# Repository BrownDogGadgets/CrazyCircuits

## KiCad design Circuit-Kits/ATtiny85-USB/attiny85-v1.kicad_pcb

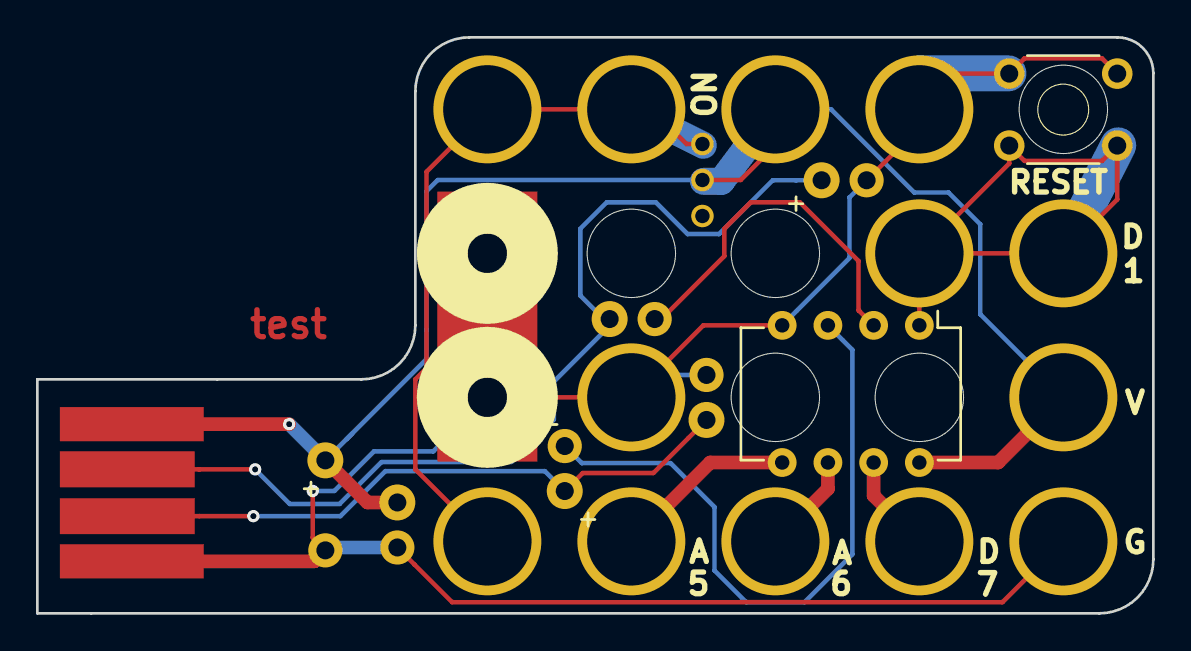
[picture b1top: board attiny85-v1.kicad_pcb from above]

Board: 2 copper layers, 62.0 x 32.0 mm, 18 parts (0 on the bottom side), 11 nets.

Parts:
BT1: Battery; CR2032-1x4
C1: 100nF; STANDALONE-2.54MM-TH
C2: 10uF; STANDALONE-5MM-TH
D1, D2: Z3v6; STANDALONE-2.54MM-TH
IC1: ATTINY85-P; DIP8-PLATFORM-TEST-NARROW
P1, P5, P6, P7: TEST_1P; STANDALONE-LEGO-HOLE-PLATED
P2: USB_PCB; USB-A-PCB-TRACES
PAD: HOLE; STANDALONE-LEGO-HOLE-PLATED
PAD#2, PAD#3: HOLE; STANDALONE-LEGO-HOLE-PLATED
R1, R2: 220; STANDALONE-2.54MM-TH
SW1: SW_PUSH; BUTTON-1x3-90DEGREE-TH-OMRON-B3F-1XXX
SW2: SLIDE; SWITCH-SPDT-3PIN-2.5mmPITCH-TH-2x2-A

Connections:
GND: BT1.GND, C1.2, C2.2, D1.2, D2.2, IC1.4, P2.4, PAD#2.1, PAD#3.1, SW1.1
unnamed: BT1.1, SW2.3
unnamed: D1.1, P2.3, R2.1
unnamed: D2.1, P2.2, R1.1
unnamed: IC1.1, P1.1, SW1.2
unnamed: IC1.2, R1.2
unnamed: IC1.3, R2.2
unnamed: IC1.5, P5.1
unnamed: IC1.6, P6.1
unnamed: IC1.7, P7.1
VCC: C1.1, C2.1, IC1.8, P2.1, PAD.1, SW2.2

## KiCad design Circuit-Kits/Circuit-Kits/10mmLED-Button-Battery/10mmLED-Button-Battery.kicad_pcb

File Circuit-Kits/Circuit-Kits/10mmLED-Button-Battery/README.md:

<!--- start title --->
# 10mmLED-Button-Battery Circuit Kit v1.3

- Updated: 7 Oct 2017

- Website: http://browndoggadgets.com/
- Company: Brown Dog Gadgets
- License: All rights reserved.

<!--- end title --->

Circuit kit that can be snapped apart into three Lego-compatible modules. Just add a coin cell battery and light the LED by pressing the pushbutton.

<!--- start bom --->

|Ref|Qty|Description|Digikey PN|
|---|---|-----------|------|
|BT1|1|HOLDER BATT COIN CR2032/20MM|952-1735-1-ND|
|LED1|1|LED GREEN 10MM DIA 2.54MM PITCH TH|754-1898-ND|
|SW1|1|SWITCH TACTILE SPST-NO 0.05A 24V|SW400-ND|

<!--- end bom --->

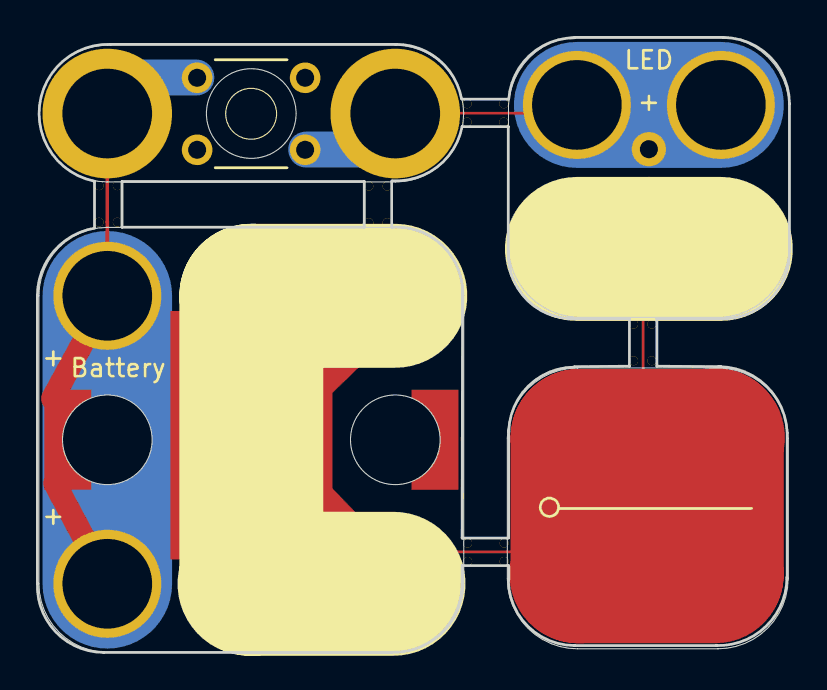
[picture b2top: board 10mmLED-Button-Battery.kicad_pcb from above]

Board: 2 copper layers, 41.8 x 34.2 mm, 4 parts (0 on the bottom side), 3 nets.

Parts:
BT1: Battery; CR2032-3x3
LED1: LED; LED-2.54MM-TH-2x2
LOGO: Val**; LOGO-CRAZY-2x2
SW1: Pushbutton; BUTTON-1x3-TH-OMRON-B3F-1XXX

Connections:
+3V: BT1.+, SW1.1
GND: BT1.GND, LED1.-
unnamed: LED1.+, SW1.2

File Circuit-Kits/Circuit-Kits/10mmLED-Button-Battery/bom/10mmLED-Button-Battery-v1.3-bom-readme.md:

|Ref|Qty|Description|Digikey PN|
|---|---|-----------|------|
|BT1|1|HOLDER BATT COIN CR2032/20MM|952-1735-1-ND|
|LED1|1|LED GREEN 10MM DIA 2.54MM PITCH TH|754-1898-ND|
|SW1|1|SWITCH TACTILE SPST-NO 0.05A 24V|SW400-ND|

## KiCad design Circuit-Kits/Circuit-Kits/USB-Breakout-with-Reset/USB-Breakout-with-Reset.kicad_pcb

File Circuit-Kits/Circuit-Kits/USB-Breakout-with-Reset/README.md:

<!--- start title --->
# USB-Breakout-with-Reset v1.0

- Updated: 14 Feb 2017
- Website: http://browndoggadgets.com/
- Company: Brown Dog Gadgets
- License: All rights reserved.

<!--- end title --->

Circuit kit module to break out USB + and - signals, along with a RESET pushbutton, to program Rewire Circuit microcontrollers in place. 

<!--- start bom --->

|Refdes|Qty|Description|Digikey Number|
|------|---|-----------|--------------|
|C1|1|CAP CER 1UF 16V X7R RADIAL|445-8614-ND|
|D1,D2|2|DIODE ZENER 3.6V 1W DO41|BZX85C3V6-ND|
|J1|1|USB MICRO-B RECEPTACLE 5PIN SMT|609-4616-1-ND|
|R1|1|RES 1.5K OHM 1/2W 5% CF MINI|S1.5KHCT-ND|
|R2,R3|2|RES 66.5 OHM 1/4W 1% AXIAL|66.5XBK-ND|
|SW1|1|SWITCH TACTILE SPST-NO 0.05A 24V|SW400-ND|

<!--- end bom --->

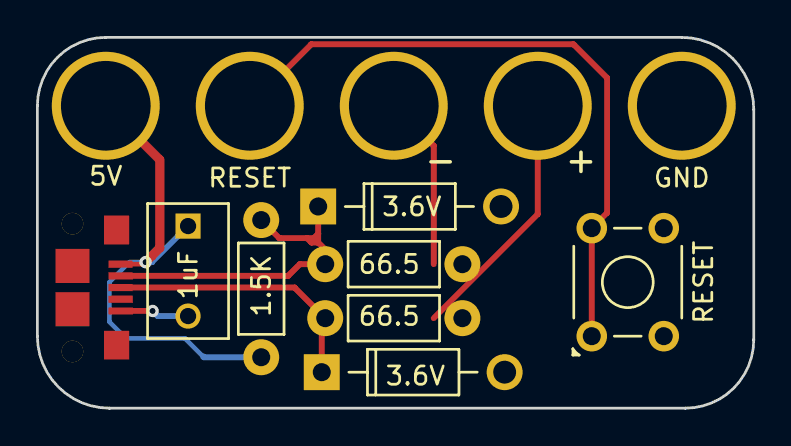
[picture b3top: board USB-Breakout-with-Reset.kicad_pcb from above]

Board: 2 copper layers, 39.8 x 20.6 mm, 13 parts (0 on the bottom side), 7 nets.

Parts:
C1: 1uf; CAP-DISC-D7.5MM-P5MM
D1, D2: 3.6V; DIODE-DO-41
J1: USB-MICRO; CONN-USB-MICRO-B-AMPHENOL-10118193-0001LF
R1: 1.5K; RES-CARBONFILM-7MM
R2, R3: 66.5; RES-CARBONFILM-7MM
SW1: RESET; SWITCH-OMRON-MOMENTARY-TH-B3F-10XX
W1, W2, W3, W4, W5: TEST_1P; STANDALONE-LEGO-HOLE-PLATED

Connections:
/DM: R2.1, W2.1
/DP: R3.1, W3.1
/RESET: SW1.1, SW1.2, W4.1
GND: C1.2, D1.2, D2.2, J1.5, SW1.3, SW1.4, W5.1
unnamed: D1.1, J1.2, R1.2, R2.2
unnamed: D2.1, J1.3, R3.2
VUSB: C1.1, J1.1, R1.1, W1.1

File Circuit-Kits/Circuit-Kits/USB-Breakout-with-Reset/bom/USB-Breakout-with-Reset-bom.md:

|Ref|Qty|Description|Digikey PN|
|---|---|-----------|------|
|C1|1|CAP CER 1UF 16V X7R RADIAL|445-8614-ND|
|D1 D2|2|DIODE ZENER 3.6V 1W BZX85C3V6 DO41|BZX85C3V6-ND|
|J1|1|USB MICRO-B RECEPTACLE 5PIN SMT R/A STUDS|609-4616-1-ND|
|R1|1|RES 1.5K OHM 1/2W 5% CF MINI|S1.5KHCT-ND|
|R2 R3|2|RES 66.5 OHM 1/4W 1% AXIAL|66.5XBK-ND|
|SW1|1| SWITCH TACTILE SPST-NO 0.05A 24V |SW400-ND|
